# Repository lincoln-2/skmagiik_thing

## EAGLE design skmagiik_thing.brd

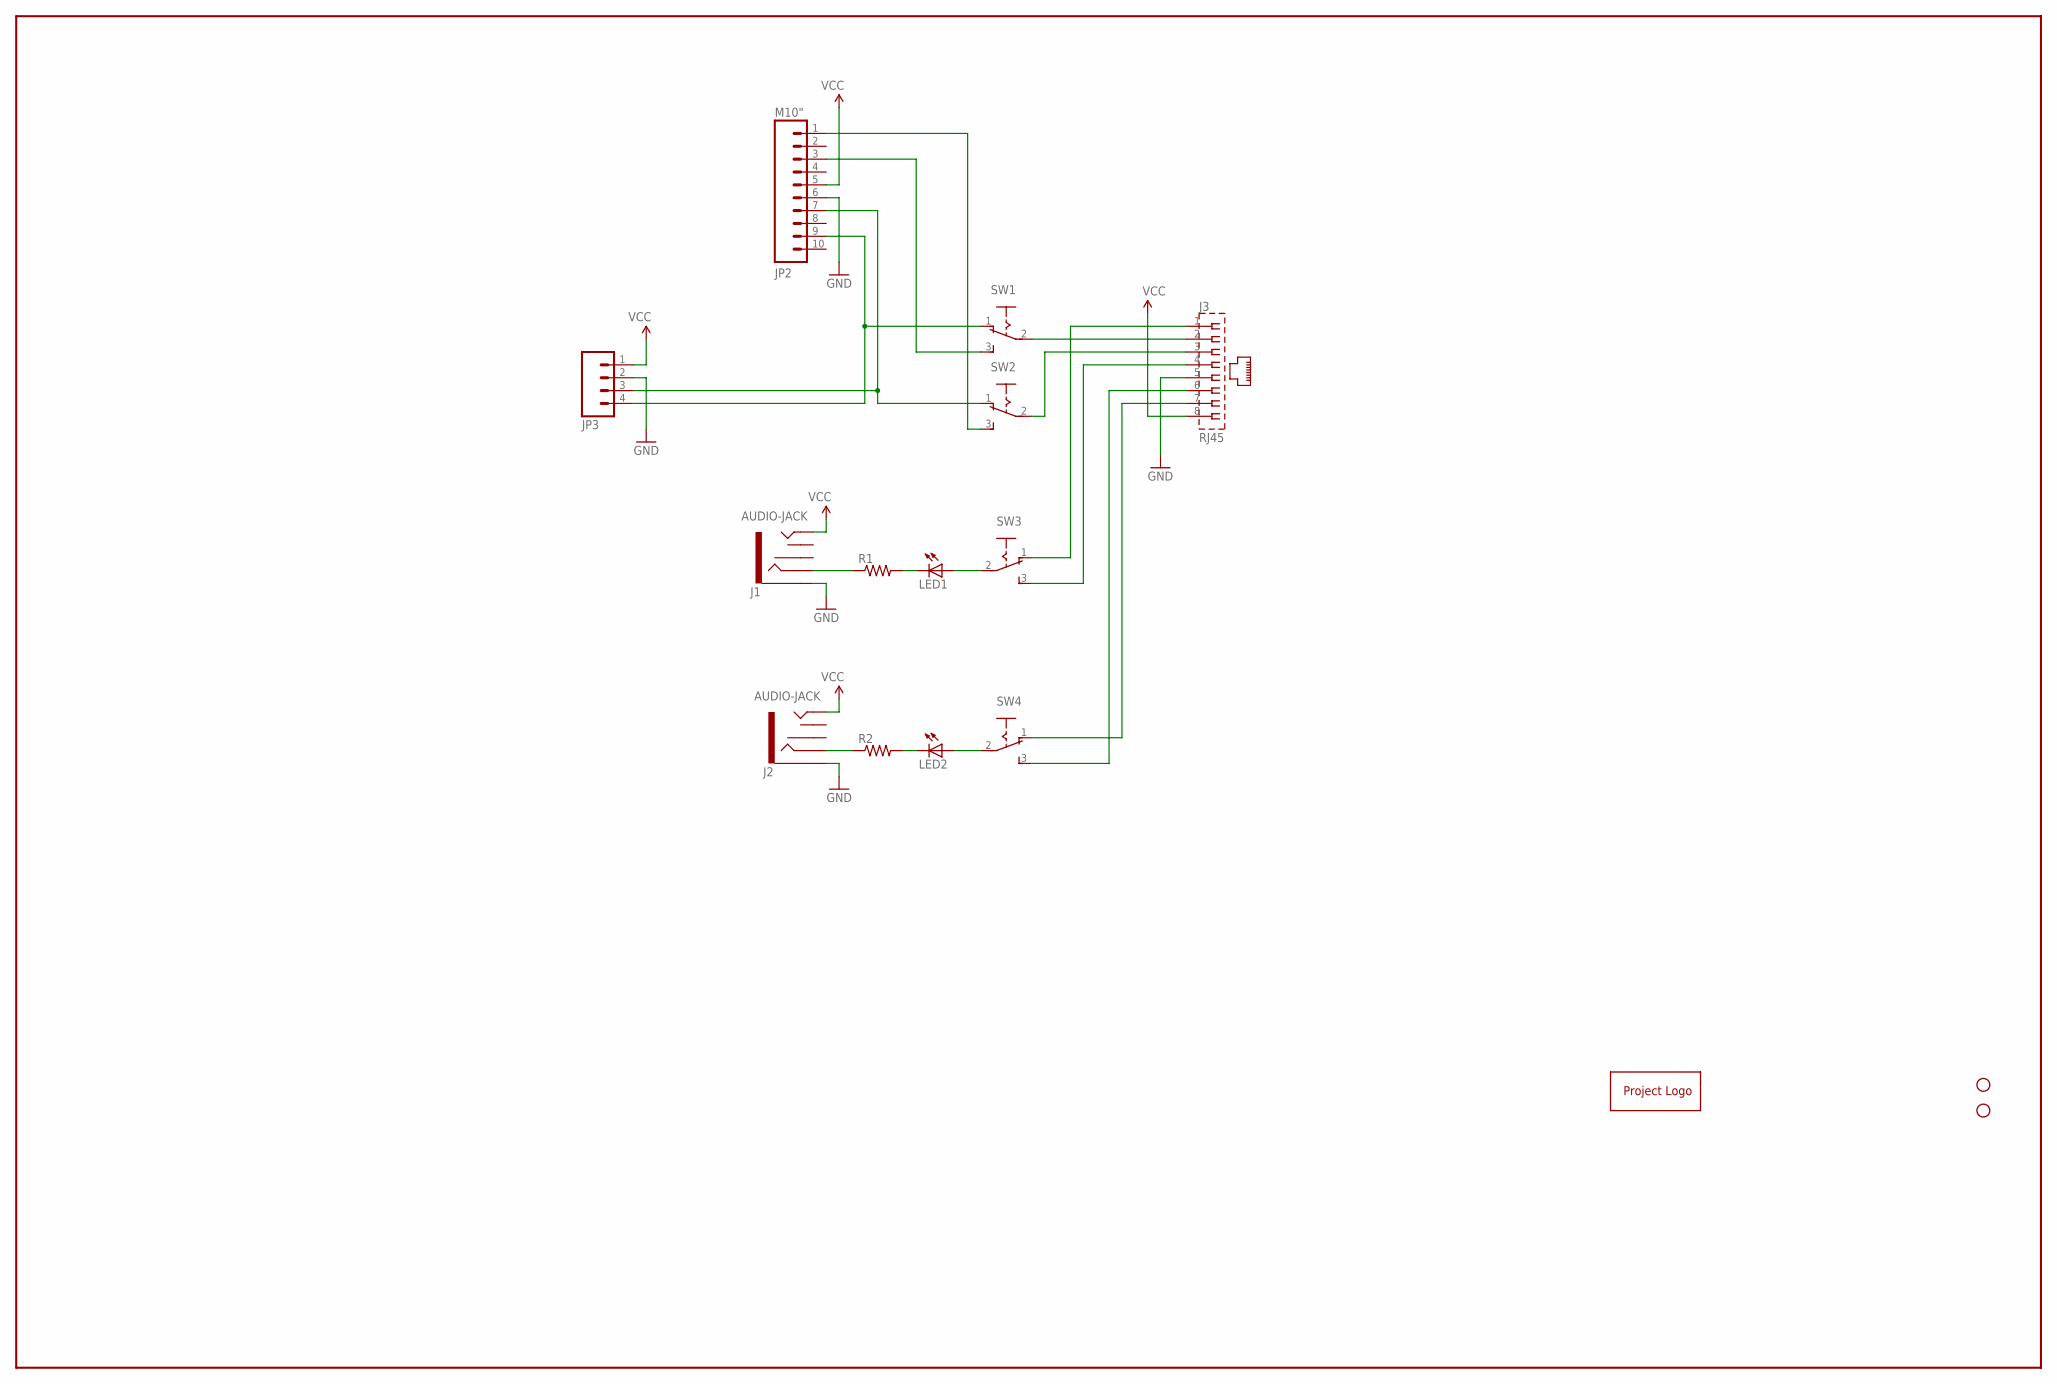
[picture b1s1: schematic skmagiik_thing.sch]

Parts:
J1, J2: AUDIO-JACK
J3: RJ45
JP2: M10"; 1X10
JP3: M04PTH; 1X04
LED1, LED2: LED3MM
R1, R2: R-US_0207/10; 0207/10
STANDOFF3, STANDOFF5: STAND-OFF
SW1, SW2, SW3, SW4: M251
U$2: PROJECT_LOGO; BMP_TEST

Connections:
GND: J1.SLEEVE, J2.SLEEVE, J3.5, JP2.6, JP3.2
unnamed: J2.RING, R2.1
unnamed: J1.RING, R1.1
unnamed: J3.7, SW4.1 (O)
unnamed: J3.6, SW4.3 (S)
unnamed: J3.4, SW3.3 (S)
unnamed: J3.1, SW3.1 (O)
unnamed: LED2.A, SW4.2
unnamed: LED1.A, SW3.2
unnamed: JP2.7, JP3.3, SW2.1 (O)
unnamed: JP2.1, SW2.3 (S)
unnamed: JP2.9, JP3.4, SW1.1 (O)
unnamed: LED1.K (C), R1.2
unnamed: JP2.3, SW1.3 (S)
unnamed: LED2.K (C), R2.2
unnamed: J3.2, SW1.2
unnamed: J3.3, SW2.2
VCC: J1.TIP, J2.TIP, J3.8, JP2.5, JP3.1

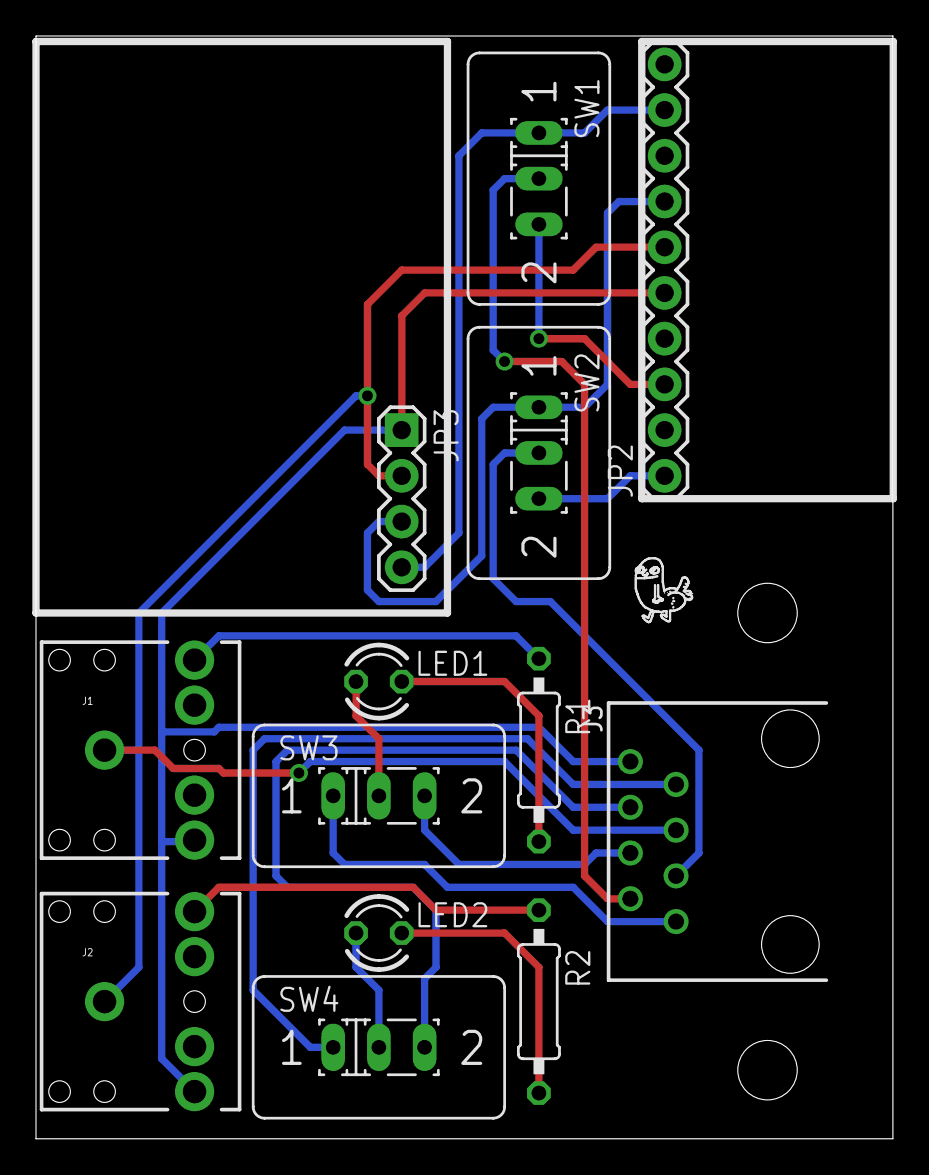
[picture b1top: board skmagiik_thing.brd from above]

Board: 2 copper layers, 47.6 x 61.3 mm, 16 parts (0 on the bottom side), 18 nets.

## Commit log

2016-01-16 added PDF of schmatic
2016-01-16 changed to use modules, added pdf of layout
2016-01-16 modifyed layout
2016-01-16 layour ready for aproval
2016-01-16 exported gerbers

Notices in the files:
parts and their libraries:
SparkFun-Electromechanical: Licensing: Creative Commons ShareAlike 4.0 International - https://creativecommons.org/licenses/by-sa/4.0
SparkFun-Aesthetics: Licensing: CC v3.0 Share-Alike You are welcome to use this library for commercial purposes.
